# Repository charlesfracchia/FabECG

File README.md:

FabECG: An Open-Source ElectroCardioGraph Device
============

by Charles Fracchia and Adam Marblestone
Copyright 2012

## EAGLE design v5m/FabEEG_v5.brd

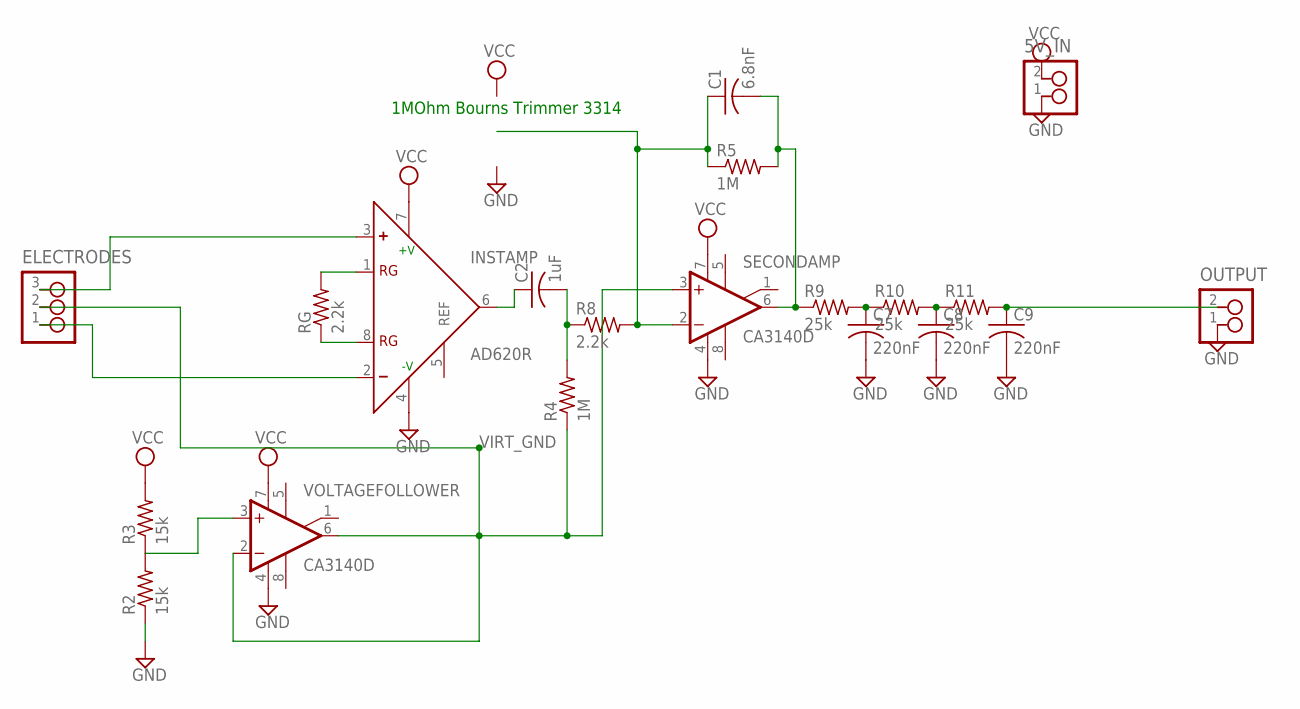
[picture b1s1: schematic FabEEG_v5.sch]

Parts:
5V_IN: 2_PIN_HEADERHEADER; SMT_PINS_2
C1: 6.8nF; C1206
C2: 1uF; C1206
C7, C8, C9: 220nF; C1206
ELECTRODES: 3_PIN_HEADERHEADER; SMT_PINS_3
INSTAMP: AD620R; SO8
OUTPUT: 2_PIN_HEADERHEADER; SMT_PINS_2
R2, R3: 15k; R1206
R4, R5: 1M; R1206
R8: 2.2k; R1206
R9, R10, R11: 25k; R1206
RG: 2.2k; R1206
SECONDAMP: CA3140D; SO08
VOLTAGEFOLLOWER: CA3140D; SO08

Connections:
GND: 5V_IN.1, C7.2, C8.2, C9.2, INSTAMP.4 (-V), OUTPUT.1, R2.1, SECONDAMP.4 (V-), VOLTAGEFOLLOWER.4 (V-)
unnamed: INSTAMP.1 (RG), RG.2
unnamed: INSTAMP.8 (RG), RG.1
unnamed: ELECTRODES.3, INSTAMP.3 (+)
unnamed: C1.2, R5.2, R9.1, SECONDAMP.6 (OUT)
unnamed: C1.1, R5.1, R8.2, SECONDAMP.2 (-IN)
unnamed: R2.2, R3.1, VOLTAGEFOLLOWER.3 (+IN)
unnamed: C2.1, INSTAMP.6 (OUT)
unnamed: C2.2, R4.2, R8.1
unnamed: C7.1, R9.2, R10.1
unnamed: ELECTRODES.1, INSTAMP.2 (-)
unnamed: C8.1, R10.2, R11.1
unnamed: C9.1, OUTPUT.2, R11.2
VCC: 5V_IN.2, INSTAMP.7 (+V), R3.2, SECONDAMP.7 (V+), VOLTAGEFOLLOWER.7 (V+)
VIRT_GND: ELECTRODES.2, R4.1, SECONDAMP.3 (+IN), VOLTAGEFOLLOWER.2 (-IN), VOLTAGEFOLLOWER.6 (OUT)

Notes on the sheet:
1MOhm Bourns Trimmer 3314

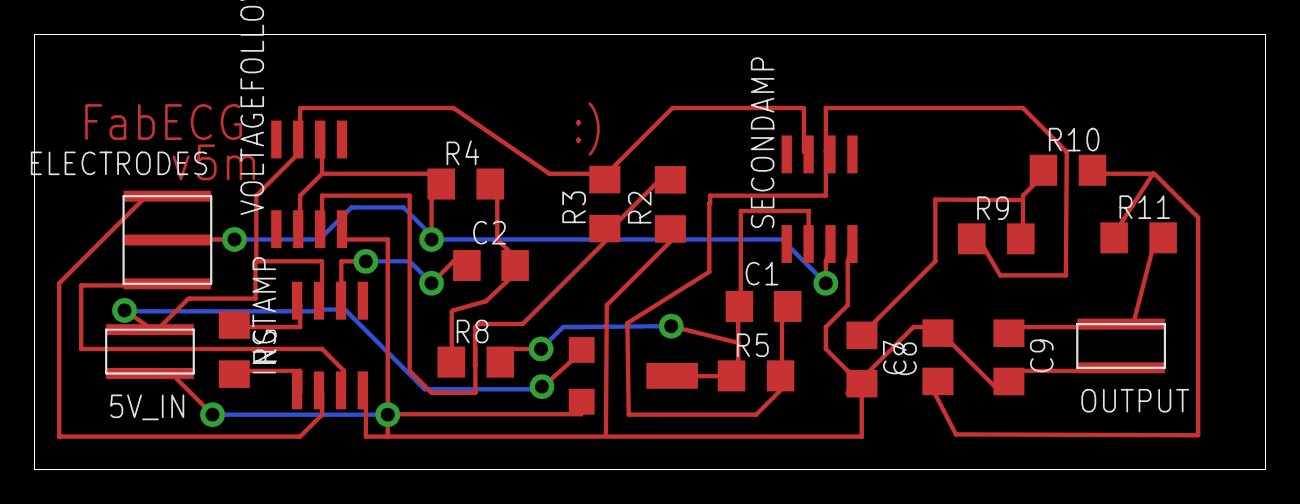
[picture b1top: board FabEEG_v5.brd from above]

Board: 2 copper layers, 71.4 x 25.2 mm, 20 parts (0 on the bottom side), 15 nets.

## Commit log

2012-10-10 Added v5m
    v5m is the last double sided board we made. It still contains the OpAmp
    based voltage follower. This is NOT a functional design, it is likely
    missing a filtering capacitor on the feedback loop of the voltage
    follower
2012-10-10 Moved v5m, added v6m
    Added v6m: single sided design with the CA3140 Voltage follower OpAmp
    removed.
    Changed structure of folder.
2012-10-11 Adam's first commit.
